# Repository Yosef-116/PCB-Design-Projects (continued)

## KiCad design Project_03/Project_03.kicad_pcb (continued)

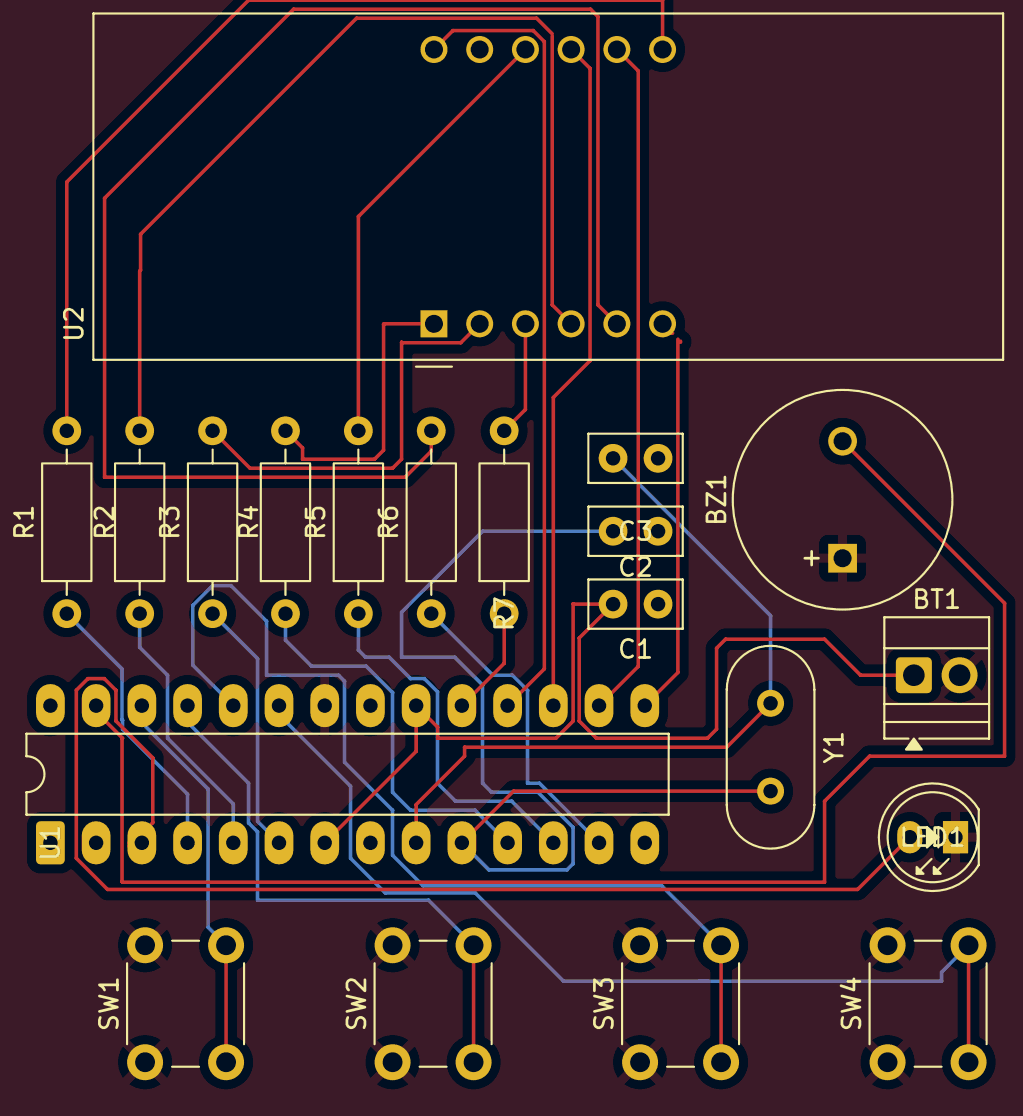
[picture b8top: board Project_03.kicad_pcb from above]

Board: 2 copper layers, 20 parts (0 on the bottom side), 28 nets.

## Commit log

2026-04-13 'README.md'
